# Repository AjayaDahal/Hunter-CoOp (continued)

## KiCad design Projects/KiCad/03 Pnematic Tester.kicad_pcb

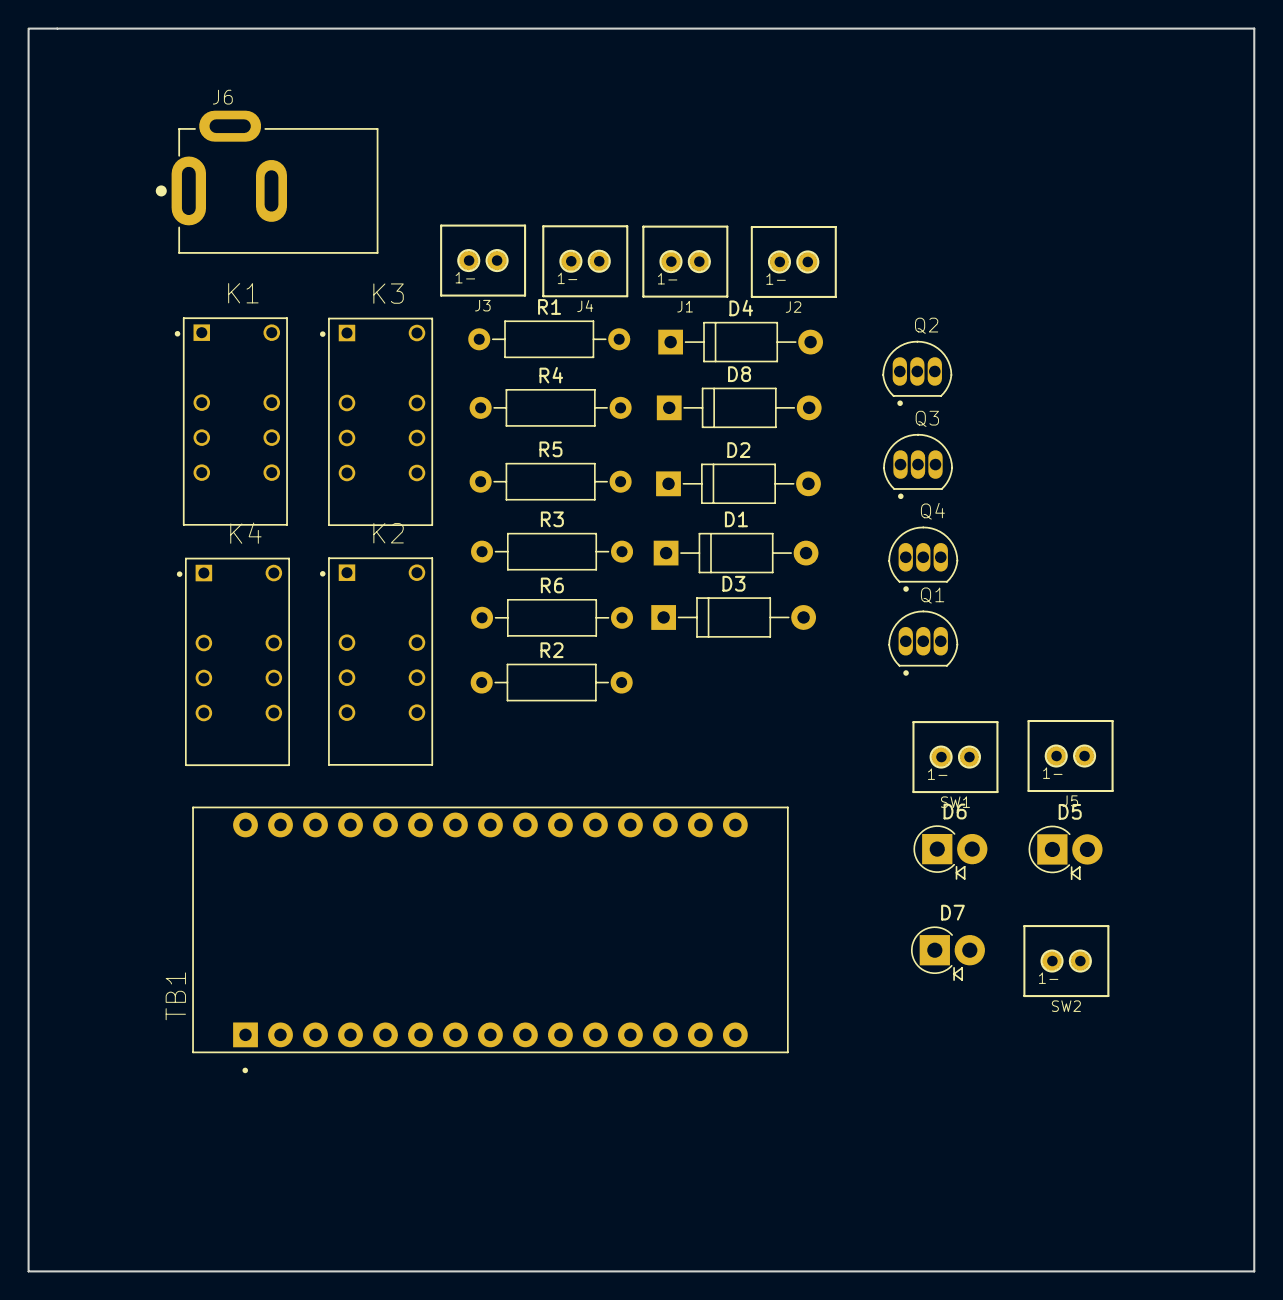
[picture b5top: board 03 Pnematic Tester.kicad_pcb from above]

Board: 2 copper layers, 89.0 x 90.2 mm, 31 parts (0 on the bottom side), 26 nets, no tracks yet.

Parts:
D1, D2, D3, D4, D8: D; D_A-405_P10.16mm_Horizontal
D5, D6, D7: LED; D_DO-41_SOD81_P2.54mm_Vertical_AnodeUp
J1: Solenoid_A POWER CONN_01X02_MALE; 2_pin_male_connector
J2: Solenoid_B POWER CONN_01X02_MALE; 2_pin_male_connector
J3, J4: POWER CONN_01X02_MALE; 2_pin_male_connector
J5: Transducer with 2 wires 4-20; 2_pin_male_connector
J6: DC adapter Main line; CUI_PJ-002A
K1, K2, K3, K4: EC2-12NU; RELAY_EC2-5NU
Q1, Q2, Q3, Q4: 2N3904; TO92127P495H495-3
R1, R2, R3, R5, R6: R; R_Axial_DIN0207_L6.3mm_D2.5mm_P10.16mm_Horizontal
R4: 10K; R_Axial_DIN0207_L6.3mm_D2.5mm_P10.16mm_Horizontal
SW1: MAIN_SWITCH; 2_pin_male_connector
SW2: PUSH to START TEST; 2_pin_male_connector
TB1: ARDUINO_NANO; SHIELD_ARDUINO_NANO

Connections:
12V: D1.1, D2.1, D3.1, D4.1, J5.1, K1.1, K1.5, K2.1, K2.5, K3.1, K3.5, K4.1, K4.5, SW1.2, TB1.30
GND: D5.1, D6.1, D7.1, J1.2, J2.2, J3.2, J4.2, J6.2, Q1.1, Q2.1, Q3.1, Q4.1, R4.2, R6.2, TB1.4, TB1.29
unnamed: D1.2, K1.12, Q1.3
unnamed: D2.2, K2.12, Q2.3
unnamed: D3.2, K3.12, Q3.3
unnamed: D4.2, K4.12, Q4.3
unnamed: D5.2, R2.2
unnamed: D6.2, R3.2
unnamed: D7.2, R1.1
unnamed: J5.2, R5.1, R6.1
unnamed: J6.1, SW1.1
unnamed: TB1.3, TB1.28
SOL_Inlet: Q1.2, TB1.5
SOL_Inlet_Ex: Q2.2, TB1.6
SOL_Inlet_Ex_Power: J3.1, K2.4
SOL_Inlet_Power: J4.1, K1.4
SOL_Outlet_Ex_Power: J1.1, K4.4
SOL_Outlet_Left: Q3.2, TB1.7
SOL_Outlet_Power: J2.1, K3.4
SOL_Outlet_Right: Q4.2, TB1.8
amberLED: R1.2, TB1.12
arduino5V: D8.1, SW2.1, TB1.27
failLED: R3.1, TB1.10
passLED: R2.1, TB1.11
pressureTransducer: D8.2, R5.2, TB1.20
pushButton: R4.1, SW2.2, TB1.9

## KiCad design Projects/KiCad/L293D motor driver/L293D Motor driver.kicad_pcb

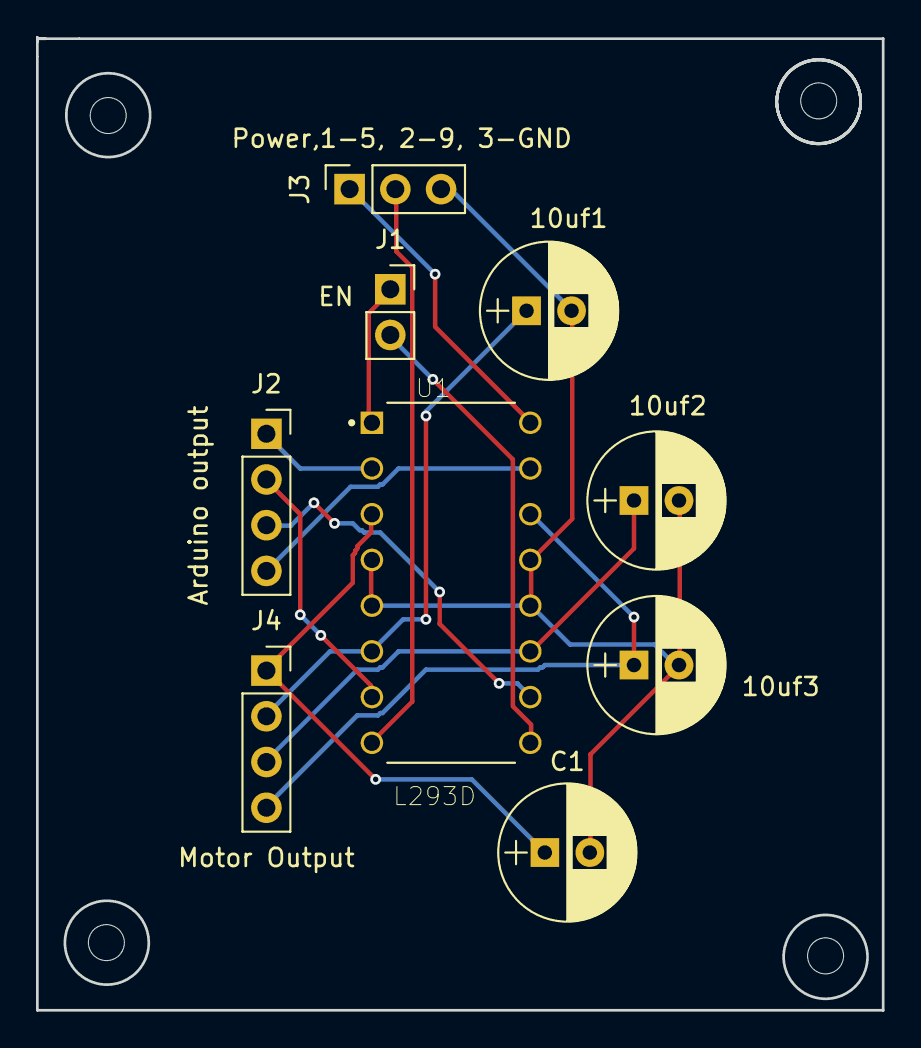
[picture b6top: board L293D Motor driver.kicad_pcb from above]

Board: 2 copper layers, 47.0 x 54.1 mm, 9 parts (0 on the bottom side), 13 nets.

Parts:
10uf1, 10uf2, 10uf3: CP; CP_Radial_D7.5mm_P2.50mm
C1: 10uf; CP_Radial_D7.5mm_P2.50mm
J1: EN; PinSocket_1x02_P2.54mm_Vertical
J2: Arduino output; PinSocket_1x04_P2.54mm_Vertical
J3: Power,1-5, 2-9, 3-GND; PinSocket_1x03_P2.54mm_Vertical
J4: Motor Output; PinSocket_1x04_P2.54mm_Vertical
U1: L293D; DIP880W50P254L2000H510Q16

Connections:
5V: J3.1, U1.16
9V: J3.2, U1.8
EN1: J1.1, U1.1
EN2: J1.2, U1.9
GND: 10uf1.2, 10uf2.2, 10uf3.2, C1.2, J3.3, U1.4, U1.5, U1.12, U1.13
Motor1A: J2.1, U1.2
Motor1AOut: C1.1, J4.1, U1.3
Motor1B: J2.2, U1.7
Motor1BOut: 10uf1.1, J4.2, U1.6
Motor2A: J2.3, U1.10
Motor2AOut: 10uf2.1, J4.3, U1.11
Motor2B: J2.4, U1.15
Motor2BOut: 10uf3.1, J4.4, U1.14

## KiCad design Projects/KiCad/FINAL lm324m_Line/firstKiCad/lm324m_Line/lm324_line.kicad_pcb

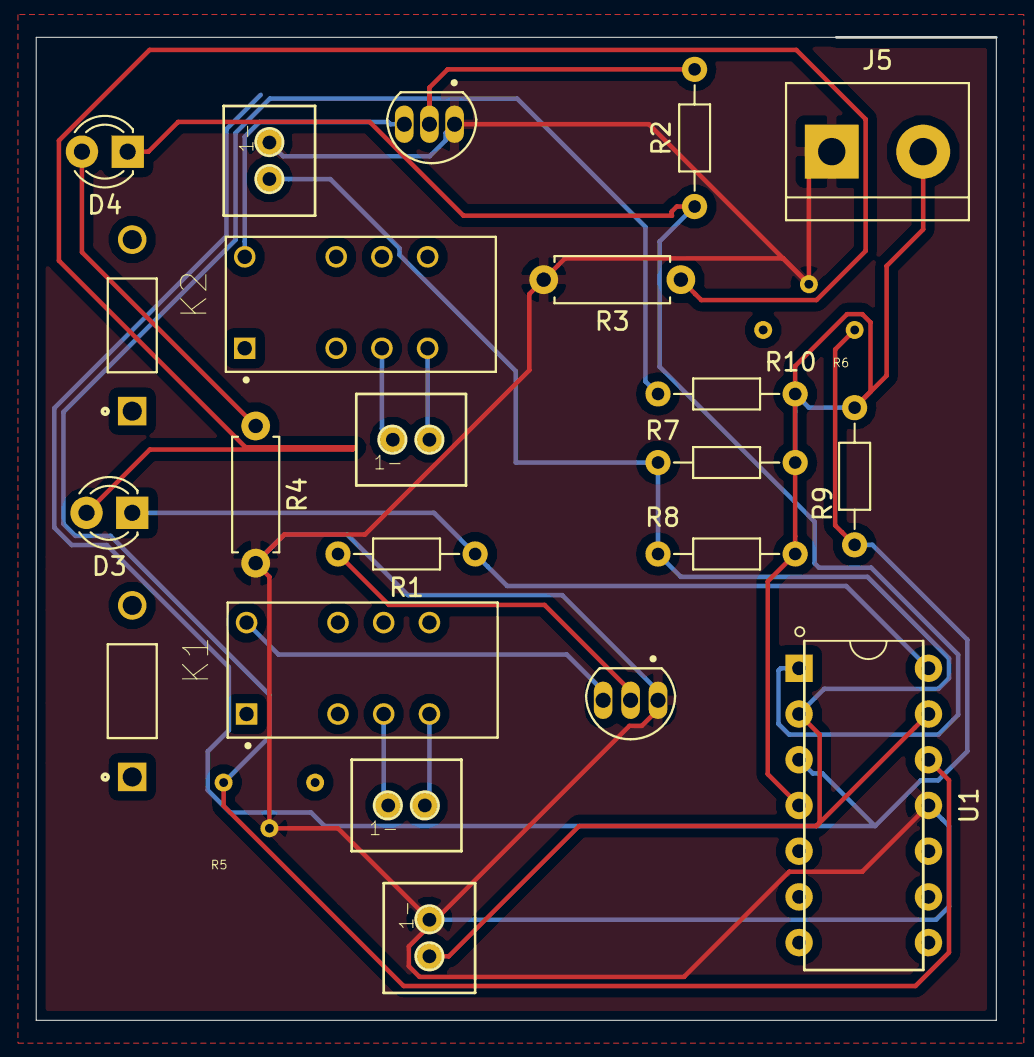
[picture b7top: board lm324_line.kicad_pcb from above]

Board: 2 copper layers, 53.3 x 54.6 mm, 24 parts (0 on the bottom side), 17 nets.

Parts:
D1, D2: 1N4001; DIOAD953W69L521D272
D3, D4: LED; LED_D3.0mm
J1, J2, J3, J4: CONN_01X02_MALE; 2_pin_male_connector
J5: Screw_Terminal_1x02; TerminalBlock_bornier-2_P5.08mm
K1, K2: EC2-5NU; RELAY_EC2-5NU
Q1, Q2: 2N3904; TO92127P495H495-3
R1, R2: 1k; R_Axial_DIN0204_L3.6mm_D1.6mm_P7.62mm_Horizontal
R3, R4: 270; R_Axial_DIN0207_L6.3mm_D2.5mm_P7.62mm_Horizontal
R5, R6: 10k; TRIM_3266W-1-103LF
R7, R8: 10k; R_Axial_DIN0204_L3.6mm_D1.6mm_P7.62mm_Horizontal
R9, R10: 470; R_Axial_DIN0204_L3.6mm_D1.6mm_P7.62mm_Horizontal
U1: lm324; LM324N

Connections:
GND: J2.1, J3.1, J5.1, Q1.1, Q2.1, R3.2, R4.2, R5.2, R6.2, U1.11
Input1+: R6.1, R9.1, U1.3
Input1-: J2.2, J3.2, R7.1, R8.2, U1.2, U1.13
Input4+: R5.1, R10.2, U1.12
unnamed: K1.12, Q1.3
unnamed: K2.12, Q2.3
unnamed: D3.2, R3.1
unnamed: D4.2, R4.1
unnamed: J1.1, K1.4
unnamed: J1.2, K1.5
unnamed: J4.1, K2.4
unnamed: J4.2, K2.5
unnamed: Q1.2, R1.2
unnamed: Q2.2, R2.2
OutputPIN1: D4.1, R2.1, U1.1
OutputPIN4: D3.1, R1.1, U1.14
V+: J5.2, R7.2, R8.1, R9.2, R10.1, U1.4

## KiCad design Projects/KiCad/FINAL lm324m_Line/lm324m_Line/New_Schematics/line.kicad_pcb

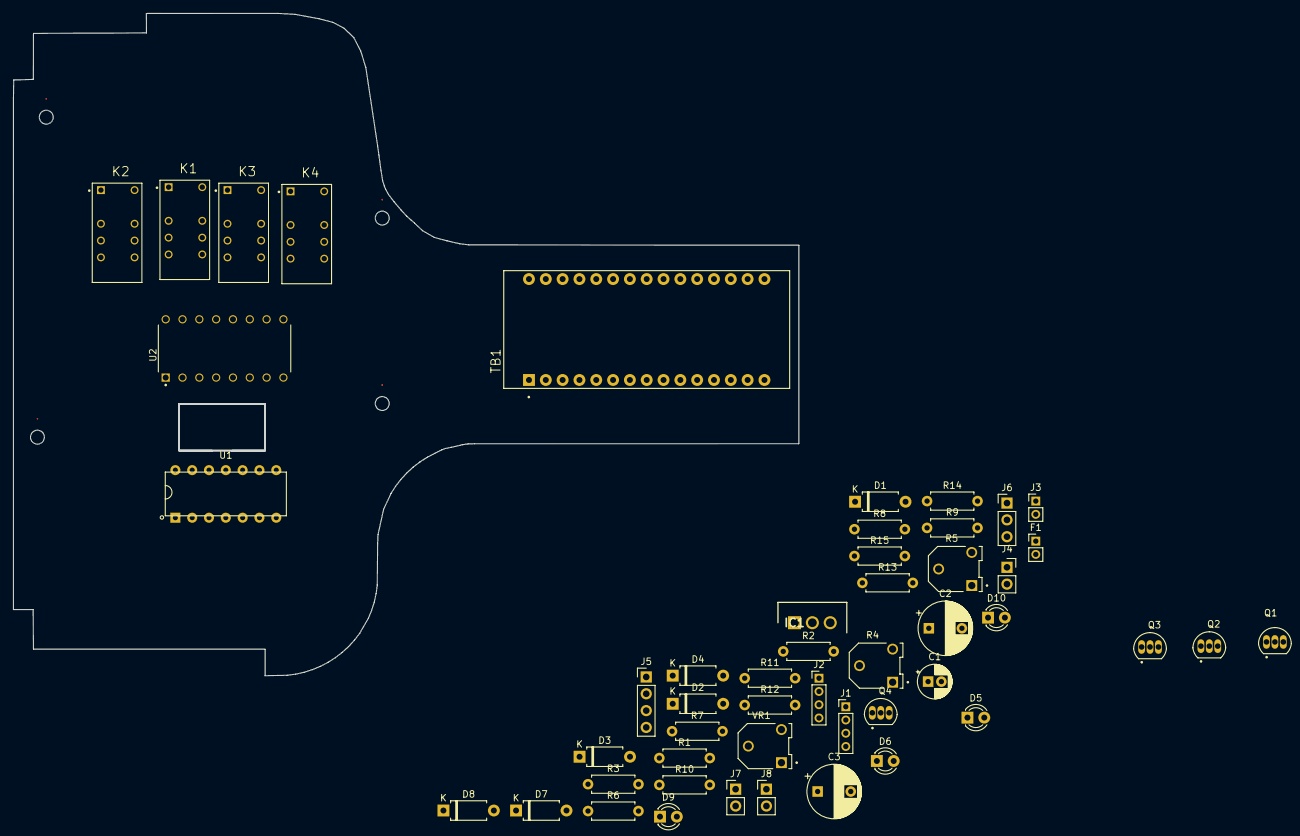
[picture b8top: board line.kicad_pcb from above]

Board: 2 copper layers, 118.6 x 100.0 mm, 54 parts (0 on the bottom side), 38 nets, no tracks yet.

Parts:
., .#2, .#3, .#4: .; MountingHole_2.1mm
C1: 0.1UF-0402-16V-10%; CP_Radial_D5.0mm_P2.00mm
C2: 10UF-0805-10V-10%; CP_Radial_D8.0mm_P5.00mm
C3: 1.0UF-0402-16V-10%; CP_Radial_D8.0mm_P5.00mm
D1, D2, D3, D4, D7, D8: 1N4001; D_A-405_P7.62mm_Horizontal
D5, D6, D9, D10: LED; LED_D3.0mm_Clear
F1: Fuse; PinHeader_1x02_P2.00mm_Vertical
IC1: LM317T; TO270P460X1020X2008-3P
J1, J2: Conn_01x04_Male; PinHeader_1x04_P2.00mm_Vertical
J3: 9V+; PinHeader_1x02_P2.00mm_Vertical
J4: PowerIN; PinSocket_1x02_P2.54mm_Vertical
J5: CONN Arduino Backup Motor driver; PinHeader_1x04_P2.54mm_Vertical
J6: CONN_01X03_MALE 1-Ard; PinHeader_1x03_P2.54mm_Vertical
J7, J8: Conn_01x02_Male; PinHeader_1x02_P2.54mm_Vertical
K1, K2, K3, K4: EC2-5NU; RELAY_EC2-5NU
Q1, Q2, Q3, Q4: 2N3904; TO92127P495H495-3
R1: 240; R_Axial_DIN0207_L6.3mm_D2.5mm_P7.62mm_Horizontal
R2, R3, R12, R13: 270; R_Axial_DIN0207_L6.3mm_D2.5mm_P7.62mm_Horizontal
R4, R5: 10k; TRIM_3306F-1-503
R6, R7, R14, R15: 1k; R_Axial_DIN0207_L6.3mm_D2.5mm_P7.62mm_Horizontal
R8, R10: 10k; R_Axial_DIN0207_L6.3mm_D2.5mm_P7.62mm_Horizontal
R9, R11: 470R; R_Axial_DIN0207_L6.3mm_D2.5mm_P7.62mm_Horizontal
TB1: ARDUINO_NANO; SHIELD_ARDUINO_NANO
U1: lm324; LM324N
U2: L293D; DIP880W50P254L2000H510Q16
VR1: 10K pot; TRIM_3306F-1-503

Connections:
5V: F1.1, J6.2
5V+ard: D3.1, D4.1, D7.1, D8.1, J1.1, J2.1, J6.1, J6.3, K1.1, K1.4, K2.1, K2.4, K3.1, K3.4, K4.1, K4.4, R8.1, R9.1, R10.1, R11.1, TB1.30, U1.4, U2.1, U2.9, U2.16
9V+: J3.2, J4.2, U2.8
Adjust: C2.1, D2.2, IC1.1, R1.2, VR1.1
GND: C1.2, C2.2, C3.2, J1.2, J2.2, J3.1, J4.1, J7.2, J8.2, Q1.1, Q2.1, Q3.1, Q4.1, R2.2, R3.2, R4.1, R5.1, R12.2, R13.2, TB1.4, TB1.29, U1.11, U2.4, U2.5, U2.12, U2.13, VR1.2
IN: C1.1, D1.1, IC1.3
Input1+: R5.2, R11.2, U1.3
Input1-: J2.3, R10.2, TB1.5, U1.2
Input4+: R4.2, R9.2, U1.12
Input4-: J1.3, R8.2, TB1.6, U1.13
L293D_Motor1a: J5.1, U2.3
L293D_Motor1b: J5.2, U2.6
L293D_Motor2a: J5.3, U2.11
L293D_Motor2b: J5.4, U2.14
Motor1a: J7.1, K1.5, K3.5
Motor2a: J8.1, K2.5, K4.5
unnamed: D3.2, K1.12, Q1.3
unnamed: D4.2, K2.12, Q2.3
unnamed: D5.2, R2.1
unnamed: D6.2, R3.1
unnamed: D7.2, K3.12, Q3.3
unnamed: D8.2, K4.12, Q4.3
unnamed: D9.2, R12.1
unnamed: D10.2, R13.1
unnamed: Q1.2, R6.2
unnamed: Q2.2, R7.2
unnamed: Q3.2, R14.2
unnamed: Q4.2, R15.2
unnamed: TB1.3, TB1.28
OUT: C3.1, D1.2, D2.1, F1.2, IC1.2, R1.1
OutputPIN1: D6.1, R7.1, U1.1
OutputPIN4: D5.1, R6.1, U1.14
analog1+: J2.4, TB1.20
analog4+: J1.4, TB1.23
arOutputPIN1: D10.1, R15.1, TB1.7, U2.2
arOutputPIN2: TB1.8, U2.7
arOutputPIN3: D9.1, R14.1, TB1.9, U2.10
arOutputPIN4: TB1.10, U2.15

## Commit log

2020-03-17 renewed
    renewed
2020-03-24 edits
2020-03-24 pull request
2020-05-14 Done
    End of term
2020-05-14 Done
    End of semester
